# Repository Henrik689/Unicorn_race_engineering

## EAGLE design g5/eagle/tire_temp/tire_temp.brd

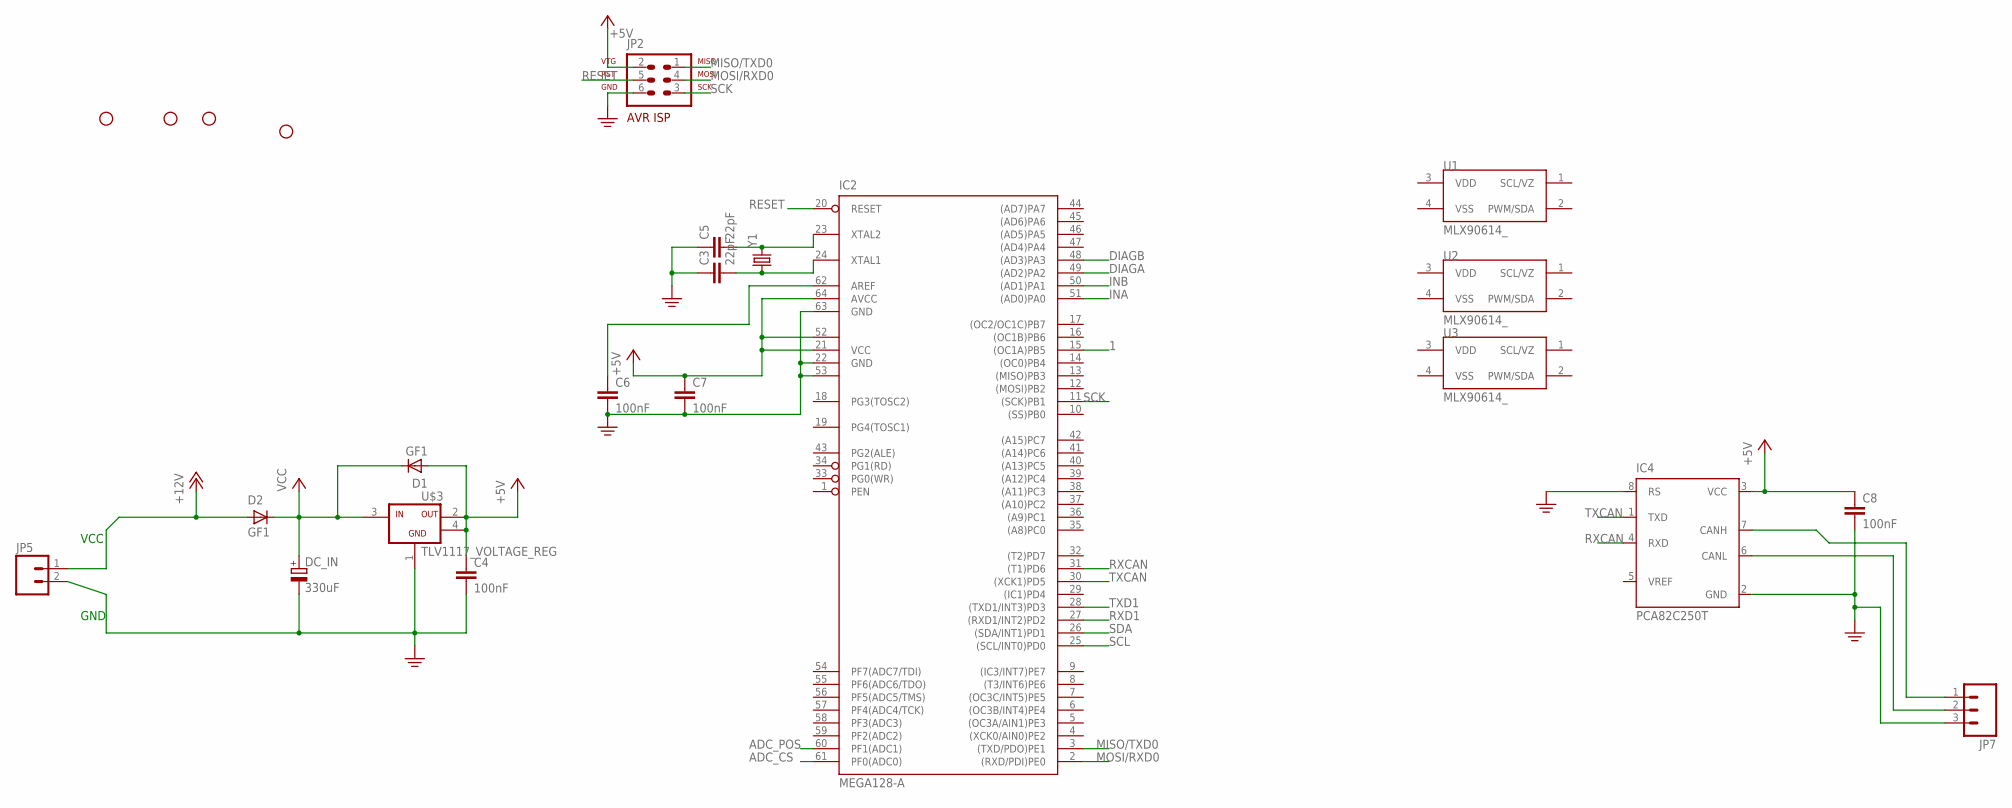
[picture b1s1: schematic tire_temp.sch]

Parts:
C3, C5: 22pF; C0603K
C4, C6, C7, C8: 100nF; C0603K
D1, D2: GF1; SMA-DO214AC
DC_IN: 330uF; E15-5
IC2: MEGA128-A; TQFP64
IC4: PCA82C250T; SO8
JP1, JP3, JP4, JP6: STAND-OFF
JP2: AVR-ISP-6
JP5: M02-JST-2MM-SMT; JST-2-SMD
JP7: M03; JST-3-SMD
U1, U2, U3: MLX90614_; TO-39
U$3: TLV1117_VOLTAGE_REG; SOT-232
Y1: CRYSTAL5X3; CRYSTAL-SMD-5X3

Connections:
1: IC2.15 ((OC1A)PB5)
+5V: C4.1, C7.1, C8.1, D1.A, IC2.21 (VCC), IC2.52 (VCC1), IC2.64 (AVCC), IC4.3 (VCC), JP2.2, U$3.2 (VOUT), U$3.4 (OUT2)
+12V: D2.A, JP5.1 (2)
ADC_CS: IC2.61 (PF0(ADC0))
ADC_POS: IC2.60 (PF1(ADC1))
CANJUMP1: IC4.7 (CANH), JP7.1
DIAGA: IC2.49 ((AD2)PA2)
DIAGB: IC2.48 ((AD3)PA3)
INA: IC2.51 ((AD0)PA0)
INB: IC2.50 ((AD1)PA1)
MISO/TXD0: IC2.3 ((TXD/PDO)PE1), JP2.1
MOSI/RXD0: IC2.2 ((RXD/PDI)PE0), JP2.4
unnamed: C3.2, IC2.24 (XTAL1), Y1.1
unnamed: C5.2, IC2.23 (XTAL2), Y1.3 (2)
unnamed: C6.1, IC2.62 (AREF)
unnamed: IC4.6 (CANL), JP7.2
PE: C3.1, C4.2, C5.1, C6.2, C7.2, C8.2, DC_IN.-, IC2.22 (GND), IC2.53 (GND1), IC2.63 (GND), IC4.2 (GND), IC4.8 (RS), JP2.6, JP5.2 (1), JP7.3, U$3.1 (GND)
RESET: IC2.20 (RESET), JP2.5
RXCAN: IC2.31 ((T1)PD6), IC4.4 (RXD)
RXD1: IC2.27 ((RXD1/INT2)PD2)
SCK: IC2.11 ((SCK)PB1), JP2.3
SCL: IC2.25 ((SCL/INT0)PD0)
SDA: IC2.26 ((SDA/INT1)PD1)
TXCAN: IC2.30 ((XCK1)PD5), IC4.1 (TXD)
TXD1: IC2.28 ((TXD1/INT3)PD3)
VCC: D1.K (C), D2.K (C), DC_IN.+, U$3.3 (VIN)

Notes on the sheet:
VCC
GND

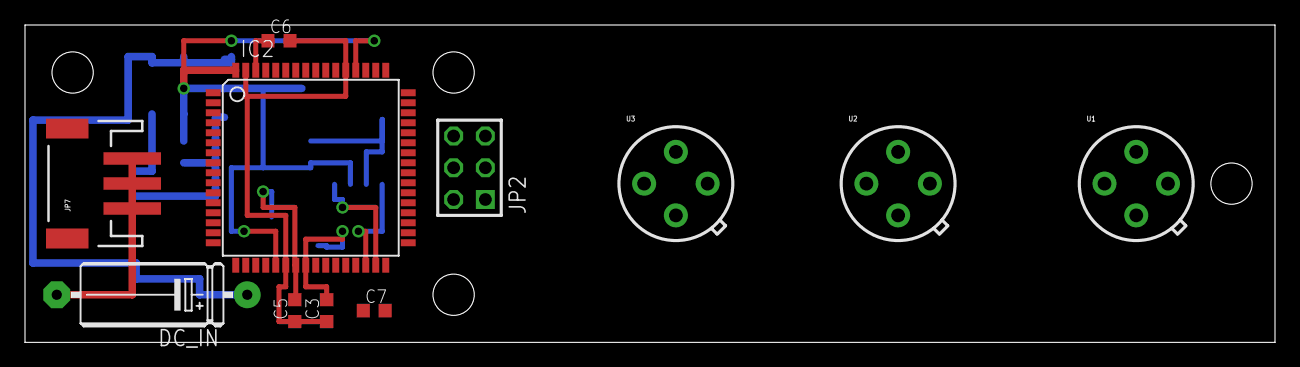
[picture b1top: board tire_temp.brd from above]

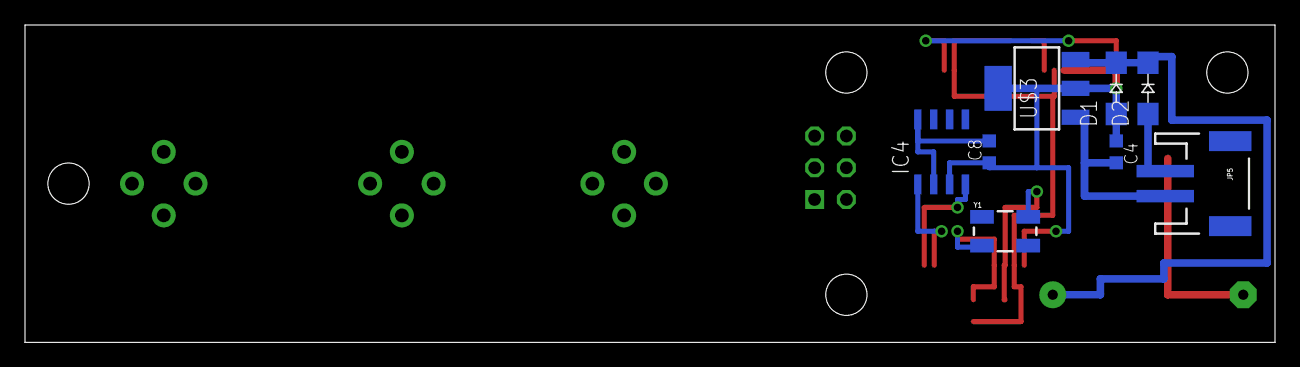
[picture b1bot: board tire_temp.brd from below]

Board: 2 copper layers, 100.0 x 25.4 mm, 23 parts (8 on the bottom side), 15 nets.

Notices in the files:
parts and their libraries:
SparkFun-Sensors: Licensing: CC v3.0 Share-Alike You are welcome to use this library for commercial purposes.
